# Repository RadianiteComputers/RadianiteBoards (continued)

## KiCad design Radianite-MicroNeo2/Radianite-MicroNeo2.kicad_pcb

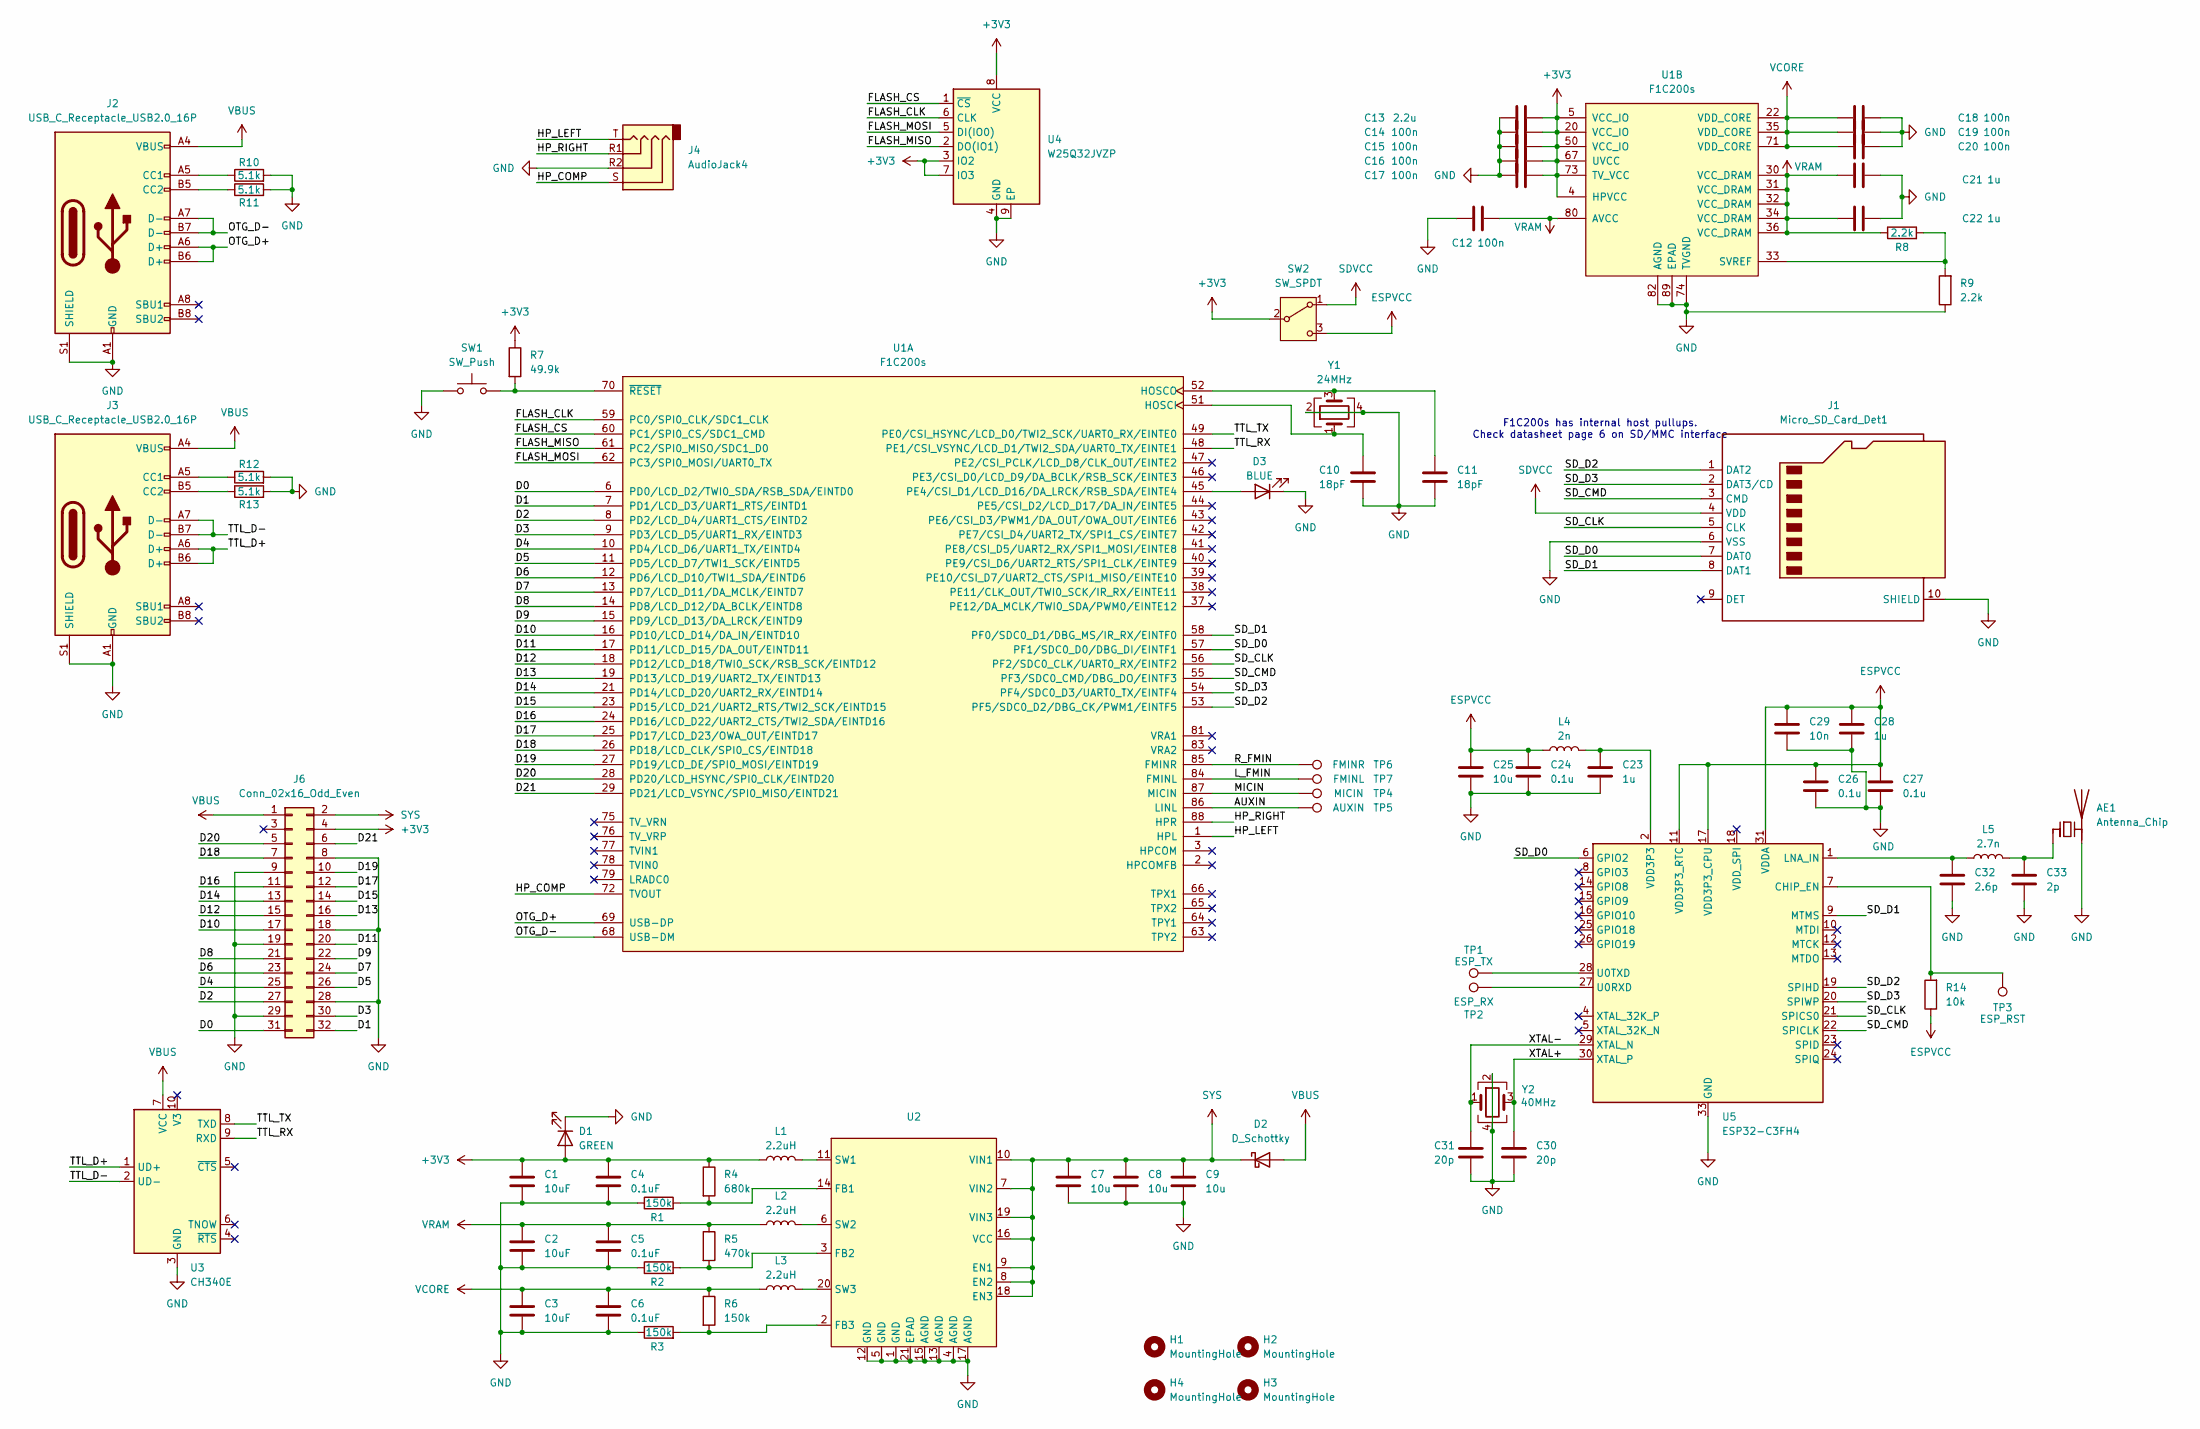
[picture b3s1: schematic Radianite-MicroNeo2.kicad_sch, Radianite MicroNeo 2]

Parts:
AE1: Antenna_Chip; U.FL_Molex_MCRF_73412-0110_Vertical
C1, C2, C3: 10uF; C_0402_1005Metric
C4, C5, C6: 0.1uF; C_0402_1005Metric
C7, C8, C9, C25: 10u; C_0402_1005Metric
C10, C11: 18pF; C_0402_1005Metric
C12, C14, C15, C16, C17, C18, C19, C20: 100n; C_0402_1005Metric
C13: 2.2u; C_0402_1005Metric
C21, C22, C23, C28: 1u; C_0402_1005Metric
C24, C26, C27: 0.1u; C_0402_1005Metric
C29: 10n; C_0402_1005Metric
C30, C31: 20p; C_0402_1005Metric
C32: 2.6p; C_0402_1005Metric
C33: 2p; C_0402_1005Metric
D1: GREEN; LED_0603_1608Metric
D2: D_Schottky; D_SOD-123F
D3: BLUE; LED_0603_1608Metric
H1, H2, H3, H4: MountingHole; MountingHole_2.1mm
J1: Micro_SD_Card_Det1; MicroSD_Plugin
J2, J3: USB_C_Receptacle_USB2.0_16P; USB_C_Receptacle_GCT_USB4105-xx-A_16P_TopMnt_Horizontal
J4: AudioJack4; Jack_3.5mm_KoreanHropartsElec_PJ-320D-4A_Horizontal
J6: Conn_02x16_Odd_Even; PinHeader_2x16_P2.54mm_Vertical
L1, L2, L3: 2.2uH; L_Changjiang_FNR252010S
L4: 2n; L_0402_1005Metric
L5: 2.7n; L_0402_1005Metric
R1, R2, R3, R6: 150k; R_0402_1005Metric
R4: 680k; R_0402_1005Metric
R5: 470k; R_0402_1005Metric
R7: 49.9k; R_0402_1005Metric
R8, R9: 2.2k; R_0402_1005Metric
R10, R11, R12, R13: 5.1k; R_0402_1005Metric
R14: 10k; R_0402_1005Metric
SW1: SW_Push; SW_Push_1P1T_NO_Vertical_Wuerth_434133025816
SW2: SW_SPDT; SW_SPDT_PCM12
TP1: ESP_TX; TestPoint_Pad_D1.0mm
TP2: ESP_RX; TestPoint_Pad_D1.0mm
TP3: ESP_RST; TestPoint_Pad_D1.0mm
TP4: MICIN; TestPoint_Pad_D1.0mm
TP5: AUXIN; TestPoint_Pad_D1.0mm
TP6: FMINR; TestPoint_Pad_D1.0mm
TP7: FMINL; TestPoint_Pad_D1.0mm
U1: F1C200s; QFN-88_EP_10x10_Pitch0.4mm
U2: WQFN-20-1EP_3x3mm_P0.4mm_EP1.7x1.7mm
U3: CH340E; MSOP-10_3x3mm_P0.5mm
U4: W25Q32JVZP; WSON-8-1EP_6x5mm_P1.27mm_EP3.4x4.3mm
U5: ESP32-C3FH4; QFN-32-1EP_5x5mm_P0.5mm_EP3.7x3.7mm
Y1: 24MHz; Crystal_SMD_3225-4Pin_3.2x2.5mm
Y2: 40MHz; Crystal_SMD_2016-4Pin_2.0x1.6mm

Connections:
+3V3: C1.1, C4.1, C13.1, C14.1, C15.1, C16.1, C17.1, D1.2 (A), J6.4, L1.1, R4.1, R7.1, SW2.2 (B), U1.4 (HPVCC), U1.5 (VCC_IO), U1.20 (VCC_IO), U1.50 (VCC_IO), U1.67 (UVCC), U1.73 (TV_VCC), U4.3 (IO2), U4.7 (IO3), U4.8 (VCC)
/AUXIN: TP5.1, U1.86 (LINL)
/D0: J6.31, U1.6 (PD0/LCD_D2/TWI0_SDA/RSB_SDA/EINTD0)
/D1: J6.32, U1.7 (PD1/LCD_D3/UART1_RTS/EINTD1)
/D2: J6.27, U1.8 (PD2/LCD_D4/UART1_CTS/EINTD2)
/D3: J6.30, U1.9 (PD3/LCD_D5/UART1_RX/EINTD3)
/D4: J6.25, U1.10 (PD4/LCD_D6/UART1_TX/EINTD4)
/D5: J6.26, U1.11 (PD5/LCD_D7/TWI1_SCK/EINTD5)
/D6: J6.23, U1.12 (PD6/LCD_D10/TWI1_SDA/EINTD6)
/D7: J6.24, U1.13 (PD7/LCD_D11/DA_MCLK/EINTD7)
/D8: J6.21, U1.14 (PD8/LCD_D12/DA_BCLK/EINTD8)
/D9: J6.22, U1.15 (PD9/LCD_D13/DA_LRCK/EINTD9)
/D10: J6.17, U1.16 (PD10/LCD_D14/DA_IN/EINTD10)
/D11: J6.20, U1.17 (PD11/LCD_D15/DA_OUT/EINTD11)
/D12: J6.15, U1.18 (PD12/LCD_D18/TWI0_SCK/RSB_SCK/EINTD12)
/D13: J6.16, U1.19 (PD13/LCD_D19/UART2_TX/EINTD13)
/D14: J6.13, U1.21 (PD14/LCD_D20/UART2_RX/EINTD14)
/D15: J6.14, U1.23 (PD15/LCD_D21/UART2_RTS/TWI2_SCK/EINTD15)
/D16: J6.11, U1.24 (PD16/LCD_D22/UART2_CTS/TWI2_SDA/EINTD16)
/D17: J6.12, U1.25 (PD17/LCD_D23/OWA_OUT/EINTD17)
/D18: J6.7, U1.26 (PD18/LCD_CLK/SPI0_CS/EINTD18)
/D19: J6.10, U1.27 (PD19/LCD_DE/SPI0_MOSI/EINTD19)
/D20: J6.5, U1.28 (PD20/LCD_HSYNC/SPI0_CLK/EINTD20)
/D21: J6.6, U1.29 (PD21/LCD_VSYNC/SPI0_MISO/EINTD21)
/FLASH_CLK: U1.59 (PC0/SPI0_CLK/SDC1_CLK), U4.6 (CLK)
/FLASH_CS: U1.60 (PC1/SPI0_CS/SDC1_CMD), U4.1 (~CS)
/FLASH_MISO: U1.61 (PC2/SPI0_MISO/SDC1_D0), U4.2 (DO(IO1))
/FLASH_MOSI: U1.62 (PC3/SPI0_MOSI/UART0_TX), U4.5 (DI(IO0))
/HP_COMP: J4.S, U1.72 (TVOUT)
/HP_LEFT: J4.T, U1.1 (HPL)
/HP_RIGHT: J4.R1, U1.88 (HPR)
/L_FMIN: TP7.1, U1.84 (FMINL)
/MICIN: TP4.1, U1.87 (MICIN)
/OTG_D+: J2.A6 (D+), J2.B6 (D+), U1.69 (USB-DP)
/OTG_D-: J2.A7 (D-), J2.B7 (D-), U1.68 (USB-DM)
/R_FMIN: TP6.1, U1.85 (FMINR)
/SD_CLK: J1.5 (CLK), U1.56 (PF2/SDC0_CLK/UART0_RX/EINTF2), U5.21 (SPICS0)
/SD_CMD: J1.3 (CMD), U1.55 (PF3/SDC0_CMD/DBG_DO/EINTF3), U5.22 (SPICLK)
/SD_D0: J1.7 (DAT0), U1.57 (PF1/SDC0_D0/DBG_DI/EINTF1), U5.6 (GPIO2)
/SD_D1: J1.8 (DAT1), U1.58 (PF0/SDC0_D1/DBG_MS/IR_RX/EINTF0), U5.9 (MTMS)
/SD_D2: J1.1 (DAT2), U1.53 (PF5/SDC0_D2/DBG_CK/PWM1/EINTF5), U5.19 (SPIHD)
/SD_D3: J1.2 (DAT3/CD), U1.54 (PF4/SDC0_D3/UART0_TX/EINTF4), U5.20 (SPIWP)
/TTL_D+: J3.A6 (D+), J3.B6 (D+), U3.1 (UD+)
/TTL_D-: J3.A7 (D-), J3.B7 (D-), U3.2 (UD-)
/TTL_RX: U1.48 (PE1/CSI_VSYNC/LCD_D1/TWI2_SDA/UART0_TX/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), U3.9 (RXD)
/TTL_TX: U1.49 (PE0/CSI_HSYNC/LCD_D0/TWI2_SCK/UART0_RX/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), U3.8 (TXD)
/XTAL+: C30.1, U5.30 (XTAL_P), Y2.3
/XTAL-: C31.1, U5.29 (XTAL_N), Y2.1
ESPVCC: C24.1, C25.1, C26.1, C27.1, C28.1, C29.1, L4.1, R14.1, SW2.3 (C), U5.11 (VDD3P3_RTC), U5.17 (VDD3P3_CPU), U5.31 (VDDA), U5.32 (VDDA)
GND: AE1.2 (PCB_Trace), C1.2, C2.2, C3.2, C4.2, C5.2, C6.2, C7.2, C8.2, C9.2, C10.2, C11.2, C12.1, C13.2, C14.2, C15.2, C16.2, C17.2, C18.2, C19.2, C20.2, C21.2, C22.2, C23.2, C24.2, C25.2, C26.2, C27.2, C28.2, C29.2, C30.2, C31.2, C32.2, C33.2, D1.1 (K), D3.1 (K), J1.6 (VSS), J1.10 (SHIELD), J2.A1 (GND), J2.A12 (GND), J2.B1 (GND), J2.B12 (GND), J2.S1 (SHIELD), J3.A1 (GND), J3.A12 (GND), J3.B1 (GND), J3.B12 (GND), J3.S1 (SHIELD), J4.R2, J6.8, J6.9, J6.18, J6.19, J6.28, J6.29, R1.1, R2.1, R3.1, R9.1, R10.2, R11.2, R12.2, R13.2, SW1.1, U1.74 (TVGND), U1.82 (AGND), U1.89 (EPAD), U2.1 (GND), U2.4 (AGND), U2.5 (GND), U2.12 (GND), U2.13 (AGND), U2.15 (AGND), U2.17 (AGND), U2.21 (EPAD), U3.3 (GND), U4.4 (GND), U4.9 (EP), U5.33 (GND), Y1.2, Y1.4, Y2.2, Y2.4
unnamed: AE1.1 (FEED), C33.1, L5.2
unnamed: C23.1, L4.2, U5.2 (VDD3P3), U5.3 (VDD3P3)
unnamed: D3.2 (A), U1.45 (PE4/CSI_D1/LCD_D16/DA_LRCK/RSB_SDA/EINT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)
unnamed: J2.A5 (CC1), R10.1
unnamed: J2.B5 (CC2), R11.1
unnamed: J3.A5 (CC1), R12.1
unnamed: J3.B5 (CC2), R13.1
unnamed: C10.1, U1.51 (HOSCI), Y1.1
unnamed: C11.1, U1.52 (HOSCO), Y1.3
unnamed: R7.2, SW1.2, U1.70 (~RESET)
unnamed: R8.2, R9.2, U1.33 (SVREF)
unnamed: R1.2, R4.2, U2.14 (FB1)
unnamed: R2.2, R5.2, U2.3 (FB2)
unnamed: R3.2, R6.2, U2.2 (FB3)
unnamed: L1.2, U2.11 (SW1)
unnamed: L2.2, U2.6 (SW2)
unnamed: L3.2, U2.20 (SW3)
unnamed: R14.2, TP3.1, U5.7 (CHIP_EN)
unnamed: C32.1, L5.1, U5.1 (LNA_IN)
unnamed: TP2.1, U5.27 (U0RXD)
unnamed: TP1.1, U5.28 (U0TXD)
SDVCC: J1.4 (VDD), SW2.1 (A)
SYS: C7.1, C8.1, C9.1, D2.1 (K), J6.2, U2.7 (VIN2), U2.8 (EN2), U2.9 (EN1), U2.10 (VIN1), U2.16 (VCC), U2.18 (EN3), U2.19 (VIN3)
VBUS: D2.2 (A), J2.A4 (VBUS), J2.A9 (VBUS), J2.B4 (VBUS), J2.B9 (VBUS), J3.A4 (VBUS), J3.A9 (VBUS), J3.B4 (VBUS), J3.B9 (VBUS), J6.1, U3.7 (VCC)
VCORE: C3.1, C6.1, C18.1, C19.1, C20.1, L3.1, R6.1, U1.22 (VDD_CORE), U1.35 (VDD_CORE), U1.71 (VDD_CORE)
VRAM: C2.1, C5.1, C12.2, C21.1, C22.1, L2.1, R5.1, R8.1, U1.30 (VCC_DRAM), U1.31 (VCC_DRAM), U1.32 (VCC_DRAM), U1.34 (VCC_DRAM), U1.36 (VCC_DRAM), U1.80 (AVCC)

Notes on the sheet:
F1C200s has internal host pullups. Check datasheet page 6 on SD/MMC interface

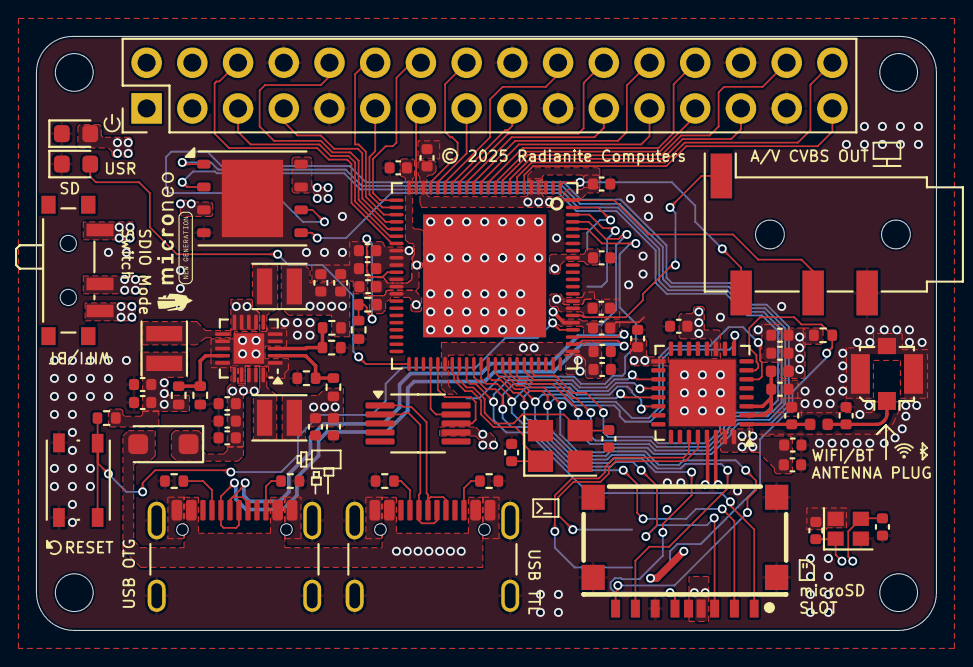
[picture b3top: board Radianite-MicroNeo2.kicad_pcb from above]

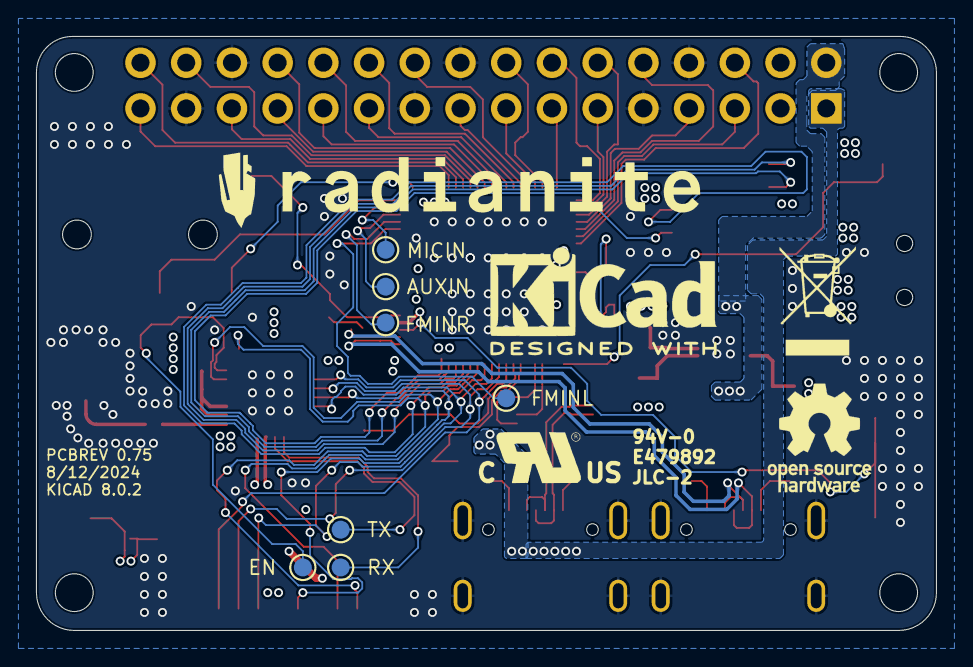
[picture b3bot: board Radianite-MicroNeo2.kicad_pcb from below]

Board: 4 copper layers, 50.0 x 33.0 mm, 81 parts (7 on the bottom side), 76 nets.

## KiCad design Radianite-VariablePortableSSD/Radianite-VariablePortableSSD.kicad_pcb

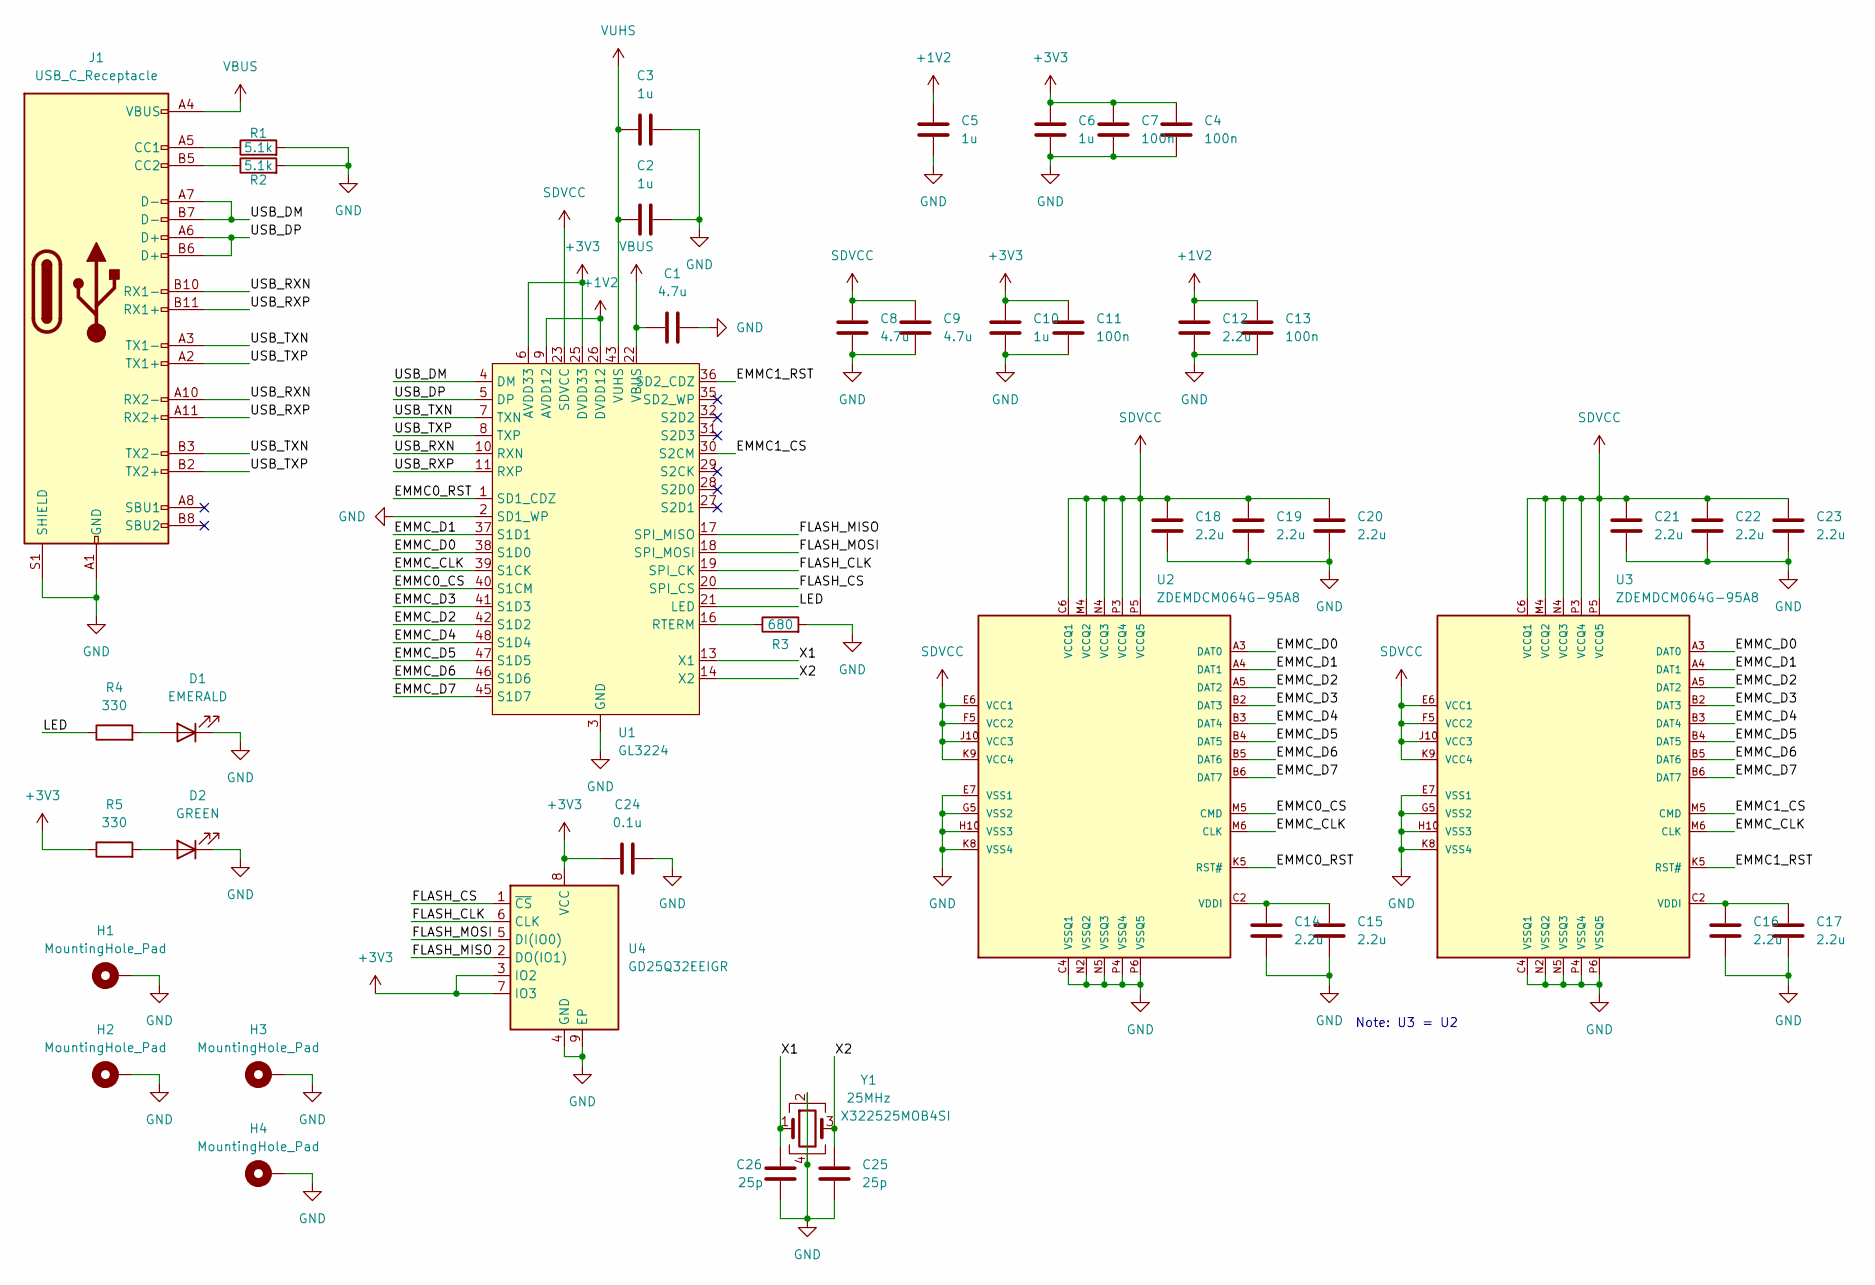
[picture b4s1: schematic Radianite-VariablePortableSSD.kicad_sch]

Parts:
C1, C8, C9: 4.7u; C_0402_1005Metric
C2, C3, C5, C6, C10: 1u; C_0402_1005Metric
C4, C7, C11, C13: 100n; C_0402_1005Metric
C12, C14, C15, C16, C17, C18, C19, C20, C21, C22, C23: 2.2u; C_0402_1005Metric
C24: 0.1u; C_0402_1005Metric
C25, C26: 25p; C_0402_1005Metric
D1: EMERALD; LED_0402_1005Metric
D2: GREEN; LED_0402_1005Metric
H1, H2, H3, H4: MountingHole_Pad; MountingHole_2.2mm_M2_Pad_Via
J1: USB_C_Receptacle; USB_C_Receptacle_Amphenol_12401610E4-2A
R1, R2: 5.1k; R_0402_1005Metric
R3: 680; R_0402_1005Metric
R4, R5: 330; R_0402_1005Metric
U1: GL3224; QFN-48-1EP_7x7mm_P0.5mm_EP5.15x5.15mm
U2, U3: ZDEMDCM064G-95A8; MICRON_EMMC_153
U4: GD25Q32EEIGR; Winbond_USON-8-1EP_3x2mm_P0.5mm_EP0.2x1.6mm
Y1: 25MHz; Crystal_SMD_3225-4Pin_3.2x2.5mm

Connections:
+1V2: C5.1, C12.1, C13.1, U1.9 (AVDD12), U1.26 (DVDD12)
+3V3: C4.1, C6.1, C7.1, C10.1, C11.1, C24.1, R5.1, U1.6 (AVDD33), U1.15 (AVDD33), U1.25 (DVDD33), U1.34 (DVDD33), U1.44 (DVDD33), U4.3 (IO2), U4.7 (IO3), U4.8 (VCC)
/EMMC0_CS: U1.40 (S1CM), U2.M5 (CMD)
/EMMC0_RST: U1.1 (SD1_CDZ), U2.K5 (RST#)
/EMMC1_CS: U1.30 (S2CM), U3.M5 (CMD)
/EMMC1_RST: U1.36 (SD2_CDZ), U3.K5 (RST#)
/EMMC_CLK: U1.39 (S1CK), U2.M6 (CLK), U3.M6 (CLK)
/EMMC_D0: U1.38 (S1D0), U2.A3 (DAT0), U3.A3 (DAT0)
/EMMC_D1: U1.37 (S1D1), U2.A4 (DAT1), U3.A4 (DAT1)
/EMMC_D2: U1.42 (S1D2), U2.A5 (DAT2), U3.A5 (DAT2)
/EMMC_D3: U1.41 (S1D3), U2.B2 (DAT3), U3.B2 (DAT3)
/EMMC_D4: U1.48 (S1D4), U2.B3 (DAT4), U3.B3 (DAT4)
/EMMC_D5: U1.47 (S1D5), U2.B4 (DAT5), U3.B4 (DAT5)
/EMMC_D6: U1.46 (S1D6), U2.B5 (DAT6), U3.B5 (DAT6)
/EMMC_D7: U1.45 (S1D7), U2.B6 (DAT7), U3.B6 (DAT7)
/FLASH_CLK: U1.19 (SPI_CK), U4.6 (CLK)
/FLASH_CS: U1.20 (SPI_CS), U4.1 (~CS)
/FLASH_MISO: U1.17 (SPI_MISO), U4.2 (DO(IO1))
/FLASH_MOSI: U1.18 (SPI_MOSI), U4.5 (DI(IO0))
/LED: R4.1, U1.21 (LED)
/USB_DM: J1.A7 (D-), J1.B7 (D-), U1.4 (DM)
/USB_DP: J1.A6 (D+), J1.B6 (D+), U1.5 (DP)
/USB_RXN: J1.A10 (RX2-), J1.B10 (RX1-), U1.10 (RXN)
/USB_RXP: J1.A11 (RX2+), J1.B11 (RX1+), U1.11 (RXP)
/USB_TXN: J1.A3 (TX1-), J1.B3 (TX2-), U1.7 (TXN)
/USB_TXP: J1.A2 (TX1+), J1.B2 (TX2+), U1.8 (TXP)
/X1: C26.1, U1.13 (X1), Y1.1
/X2: C25.1, U1.14 (X2), Y1.3
GND: C1.2, C2.2, C3.2, C4.2, C5.2, C6.2, C7.2, C8.2, C9.2, C10.2, C11.2, C12.2, C13.2, C14.2, C15.2, C16.2, C17.2, C18.2, C19.2, C20.2, C21.2, C22.2, C23.2, C24.2, C25.2, C26.2, D1.1 (K), D2.1 (K), H1.1, H2.1, H3.1, H4.1, J1.A1 (GND), J1.A12 (GND), J1.B1 (GND), J1.B12 (GND), J1.S1 (SHIELD), R1.2, R2.2, R3.2, U1.2 (SD1_WP), U1.3 (GND), U1.12 (GND), U1.49 (GND), U2.C4 (VSSQ1), U2.E7 (VSS1), U2.G5 (VSS2), U2.H10 (VSS3), U2.K8 (VSS4), U2.N2 (VSSQ2), U2.N5 (VSSQ3), U2.P4 (VSSQ4), U2.P6 (VSSQ5), U3.C4 (VSSQ1), U3.E7 (VSS1), U3.G5 (VSS2), U3.H10 (VSS3), U3.K8 (VSS4), U3.N2 (VSSQ2), U3.N5 (VSSQ3), U3.P4 (VSSQ4), U3.P6 (VSSQ5), U4.4 (GND), U4.9 (EP), Y1.2, Y1.4
unnamed: D1.2 (A), R4.2
unnamed: D2.2 (A), R5.2
unnamed: J1.A5 (CC1), R1.1
unnamed: J1.B5 (CC2), R2.1
unnamed: R3.1, U1.16 (RTERM)
unnamed: C14.1, C15.1, U2.C2 (VDDI)
unnamed: C16.1, C17.1, U3.C2 (VDDI)
SDVCC: C8.1, C9.1, C18.1, C19.1, C20.1, C21.1, C22.1, C23.1, U1.23 (SDVCC), U1.24 (SDVCC), U2.C6 (VCCQ1), U2.E6 (VCC1), U2.F5 (VCC2), U2.J10 (VCC3), U2.K9 (VCC4), U2.M4 (VCCQ2), U2.N4 (VCCQ3), U2.P3 (VCCQ4), U2.P5 (VCCQ5), U3.C6 (VCCQ1), U3.E6 (VCC1), U3.F5 (VCC2), U3.J10 (VCC3), U3.K9 (VCC4), U3.M4 (VCCQ2), U3.N4 (VCCQ3), U3.P3 (VCCQ4), U3.P5 (VCCQ5)
VBUS: C1.1, J1.A4 (VBUS), J1.A9 (VBUS), J1.B4 (VBUS), J1.B9 (VBUS), U1.22 (VBUS)
VUHS: C2.1, C3.1, U1.33 (VUHS), U1.43 (VUHS)

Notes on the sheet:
Note: U3 = U2

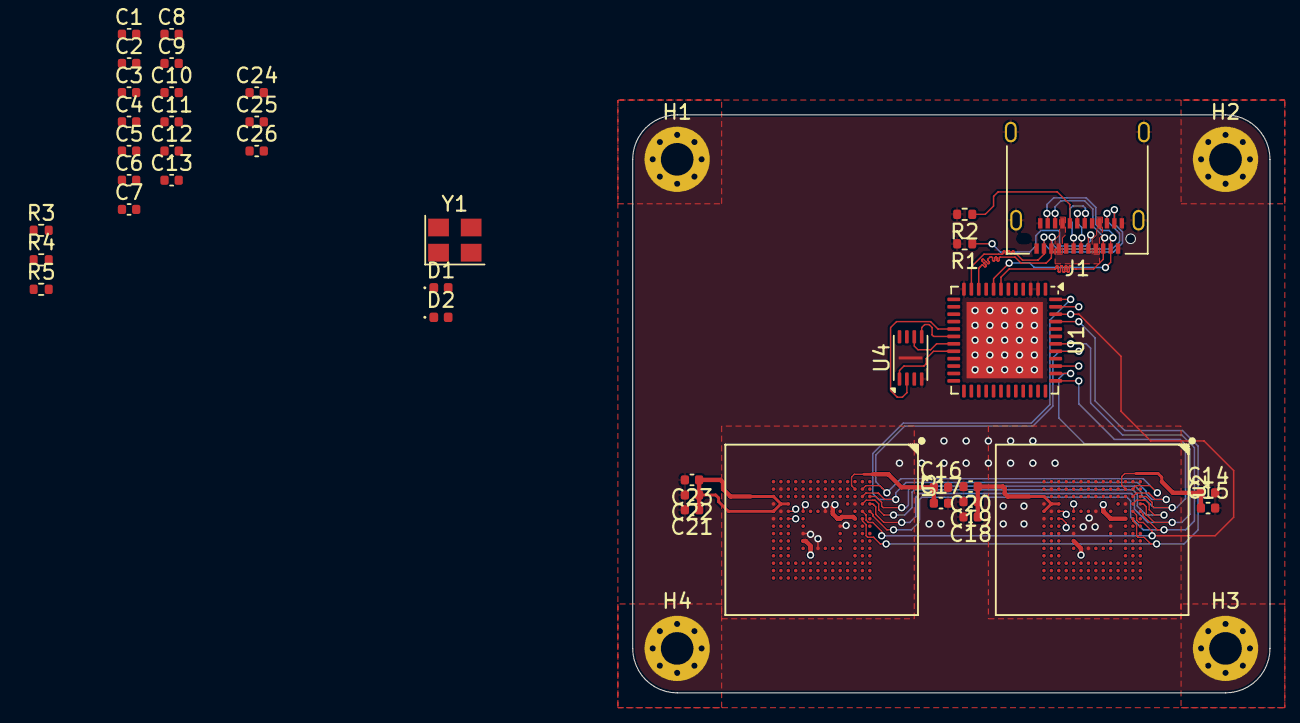
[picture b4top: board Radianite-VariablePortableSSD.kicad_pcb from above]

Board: 4 copper layers, 43.0 x 39.0 mm, 43 parts (0 on the bottom side), 39 nets.

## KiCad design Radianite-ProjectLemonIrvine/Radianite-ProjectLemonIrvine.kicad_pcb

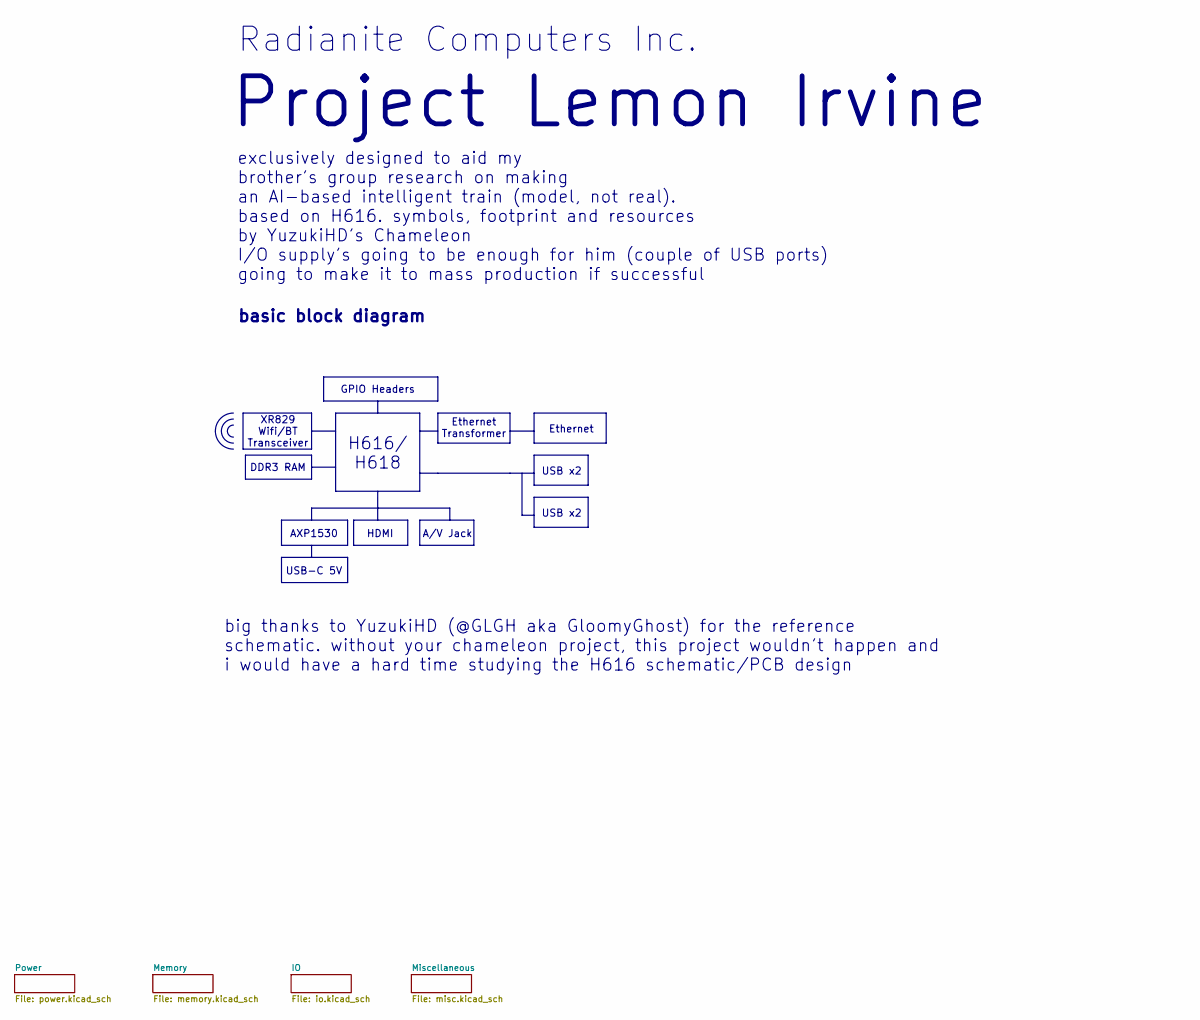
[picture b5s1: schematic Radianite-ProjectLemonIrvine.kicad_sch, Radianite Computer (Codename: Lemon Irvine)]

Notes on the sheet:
Radianite Computers Inc.
Ethernet
USB-C 5V
USB x2
A/V Jack
big thanks to YuzukiHD (@GLGH aka GloomyGhost) for the reference schematic. without your chameleon project, this project wouldn't happen and i would have a hard time studying the H616 schematic/PCB design
basic block diagram
HDMI
Ethernet Transformer
AXP1530
Project Lemon Irvine
H616/ H618
DDR3 RAM
XR829 Wifi/BT Transceiver
GPIO Headers
exclusively designed to aid my brother's group research on making an AI-based intelligent train (model, not real). based on H616. symbols, footprint and resources by YuzukiHD's Chameleon I/O supply's going to be enough for him (couple of USB ports) going to make it to mass production if successful
